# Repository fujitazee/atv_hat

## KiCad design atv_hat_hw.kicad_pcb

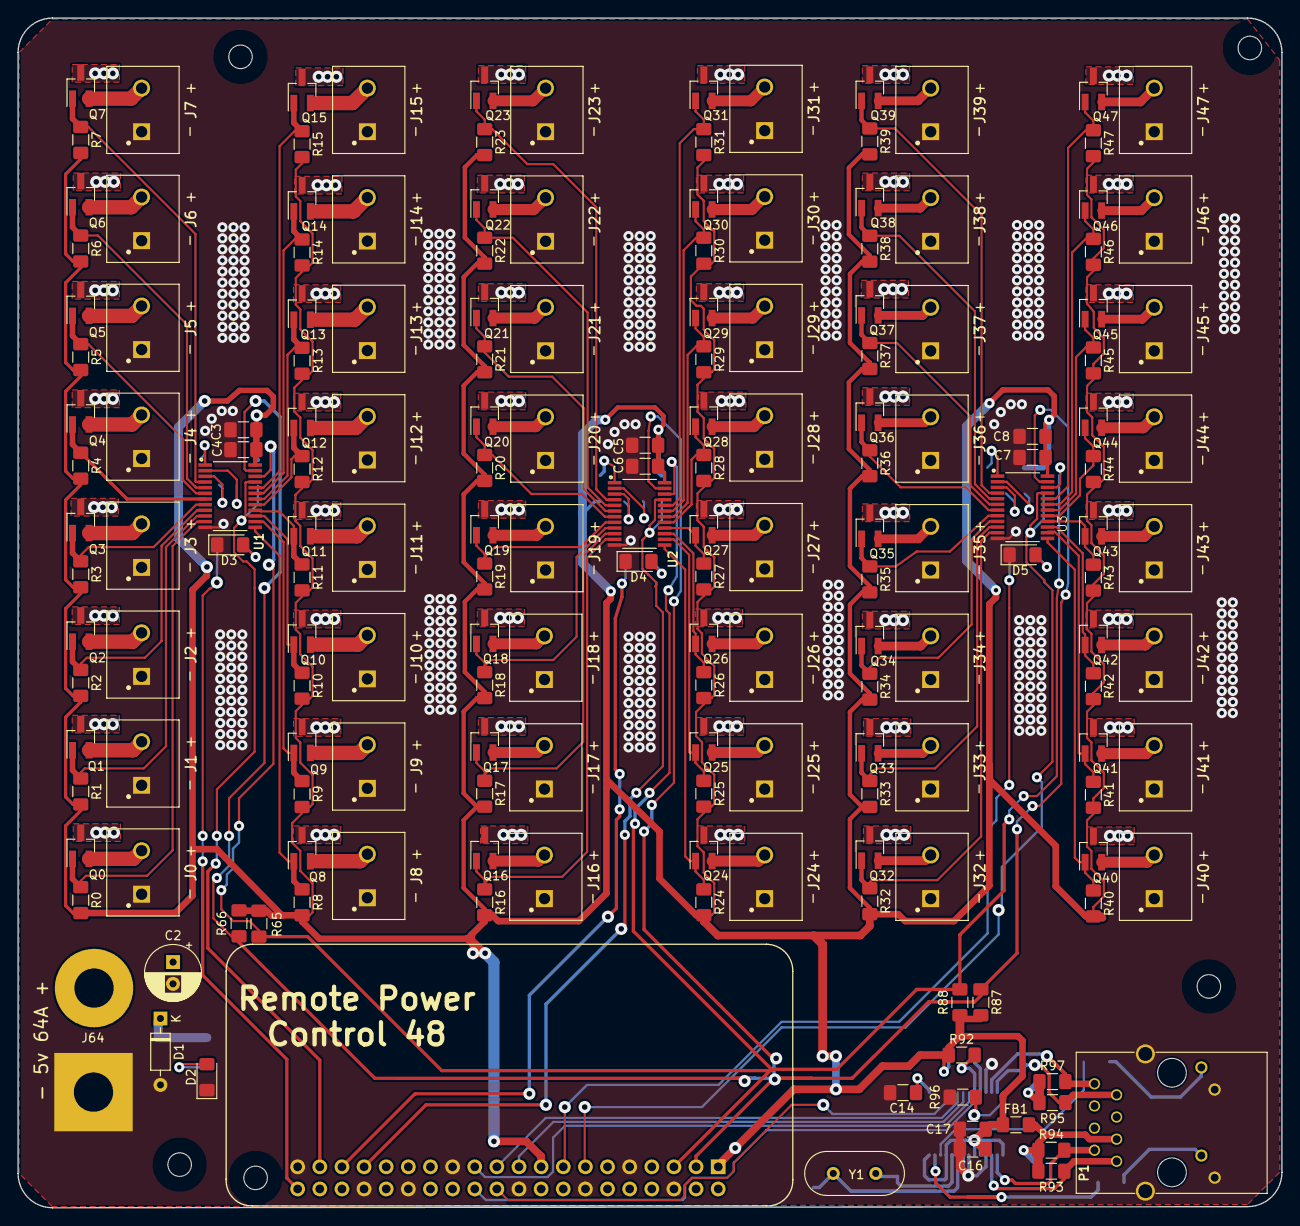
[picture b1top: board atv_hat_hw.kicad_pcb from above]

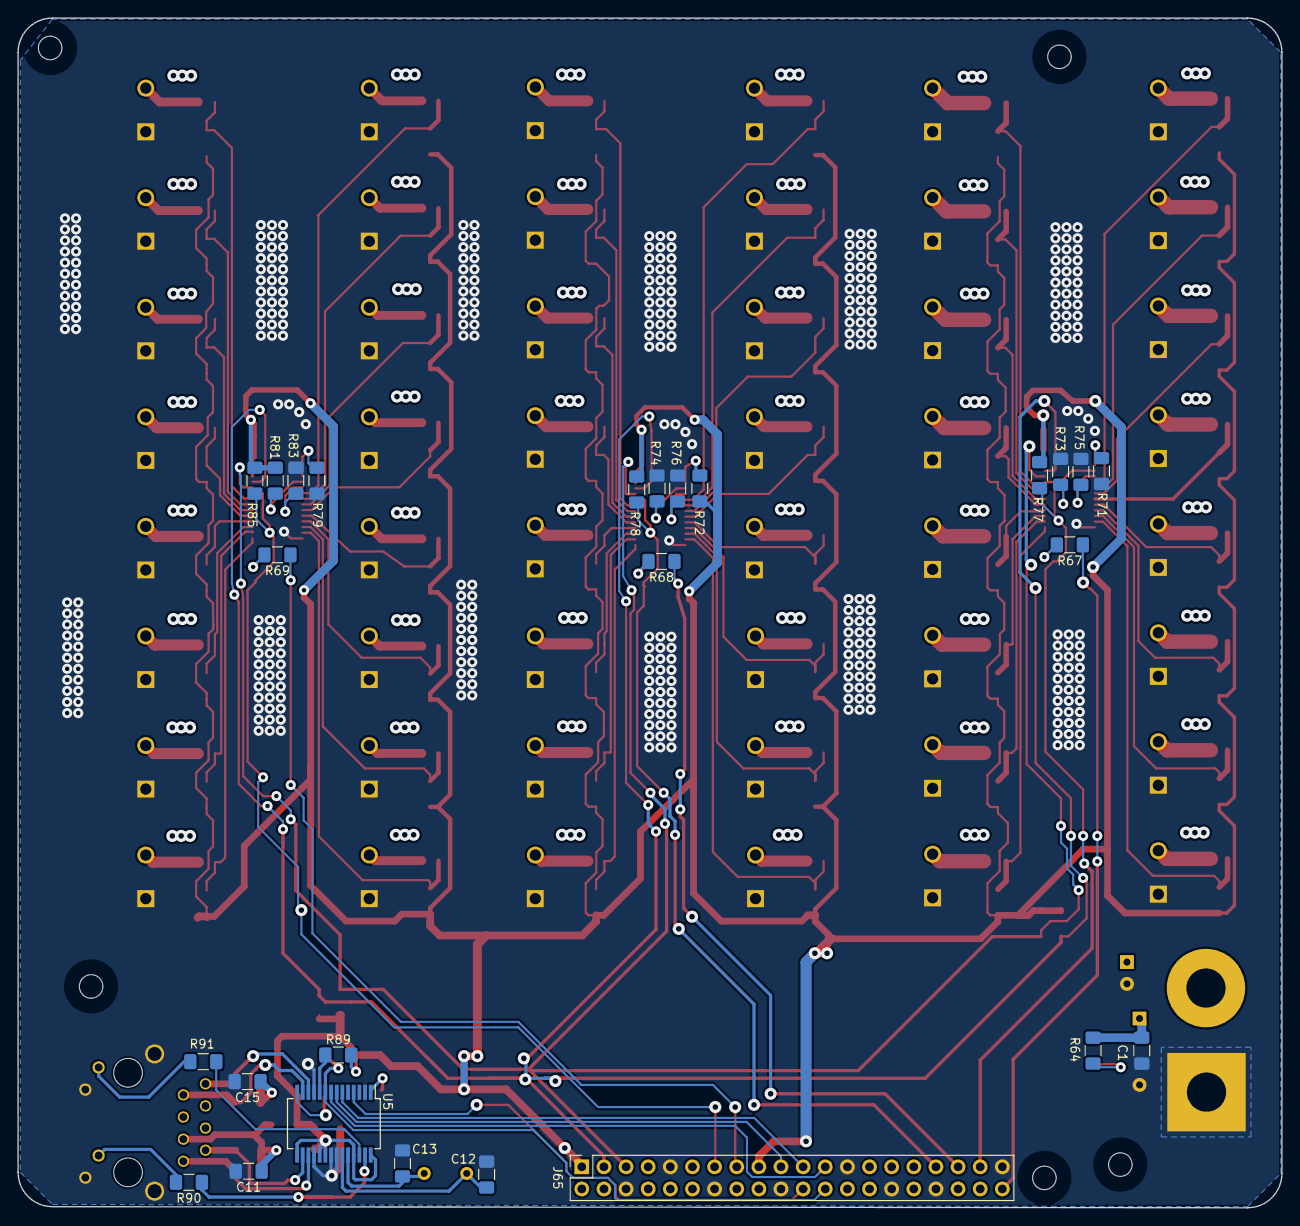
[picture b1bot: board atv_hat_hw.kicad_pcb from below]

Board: 4 copper layers, 145.0 x 136.5 mm, 207 parts (26 on the bottom side), 140 nets.

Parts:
C1, C3, C5, C7, C11, C15, C16: 100n; C_1206_3216Metric_Pad1.42x1.75mm_HandSolder
C2: 100u; CP_Radial_D6.3mm_P2.50mm
C4, C6, C8, C14, C17: 10u; C_1206_3216Metric_Pad1.42x1.75mm_HandSolder
C12, C13: 30p; C_1206_3216Metric_Pad1.42x1.75mm_HandSolder
D1: 5.6v; D_DO-35_SOD27_P7.62mm_Horizontal
D2: Blue; LED_1206_3216Metric_Pad1.42x1.75mm_HandSolder
D3, D4, D5: Green; LED_1206_3216Metric_Pad1.42x1.75mm_HandSolder
FB1: 80mA; L_1206_3216Metric_Pad1.42x1.75mm_HandSolder
H2, H2#2, H2#3, H2#4, H2#5: MountingHole; MountingHole_2.7mm_M2.5_uHAT_RPi
J0, J1, J2, J3, J4, J5, J6, J7, J8, J9, J10, J11, J12, J13, J14, J15, J16, J17, J18, J19, J20, J21, J22, J23, J24, J25, J26, J27, J28, J29, J30, J31, J32, J33, J34, J35, J36, J37, J38, J39, J40, J41, J42, J43, J44, J45, J46, J47: phoenix_1935161; PHOENIX_1935161
J64: phoenix_1935161; SolderWirePad_1x02_P9.0mm_Drill4.5mm
J65: GPIO_CONNECTOR; PinSocket_2x20_P2.54mm_Vertical_Centered_Anchor
P1: RB1-125BAG1A; WIZNET_RB1-125BAG1A
Q0, Q1, Q2, Q3, Q4, Q5, Q6, Q7, Q8, Q9, Q10, Q11, Q12, Q13, Q14, Q15, Q16, Q17, Q18, Q19, Q20, Q21, Q22, Q23, Q24, Q25, Q26, Q27, Q28, Q29, Q30, Q31, Q32, Q33, Q34, Q35, Q36, Q37, Q38, Q39, Q40, Q41, Q42, Q43, Q44, Q45, Q46, Q47: Q_NMOS_GSD; SOT-23_Handsoldering
R0, R1, R2, R3, R4, R5, R6, R7, R8, R9, R10, R11, R12, R13, R14, R15, R16, R17, R18, R19, R20, R21, R22, R23, R24, R25, R26, R27, R28, R29, R30, R31, R32, R33, R34, R35, R36, R37, R38, R39, R40, R41, R42, R43, R44, R45, R46, R47, R65, R66, R71, R72, R73, R74, R75, R76, R77, R78, R79, R81, R83, R85, R87, R88, R89, R90, R91, R92: 10k; R_1206_3216Metric_Pad1.42x1.75mm_HandSolder
R64, R67, R68, R69: 220; R_1206_3216Metric_Pad1.42x1.75mm_HandSolder
R93, R94, R95, R97: 49.9; R_1206_3216Metric_Pad1.42x1.75mm_HandSolder
R96: 2.32k; R_1206_3216Metric_Pad1.42x1.75mm_HandSolder
U1, U2, U3: PCA9552PW,118; SOP65P640X110-24N
U5: ENC28J60x-SS; SSOP-28_5.3x10.2mm_P0.65mm
Y1: Crystal; Crystal_HC49-4H_Vertical

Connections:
+3V3: C3.2, C4.2, C5.2, C6.2, C7.2, C8.2, C16.2, C17.2, FB1.1, J65.1, J65.17, R0.2, R1.2, R2.2, R3.2, R4.2, R5.2, R6.2, R7.2, R8.2, R9.2, R10.2, R11.2, R12.2, R13.2, R14.2, R15.2, R16.2, R17.2, R18.2, R19.2, R20.2, R21.2, R22.2, R23.2, R24.2, R25.2, R26.2, R27.2, R28.2, R29.2, R30.2, R31.2, R32.2, R33.2, R34.2, R35.2, R36.2, R37.2, R38.2, R39.2, R40.2, R41.2, R42.2, R43.2, R44.2, R45.2, R46.2, R47.2, R65.2, R66.2, R72.1, R77.1, R78.1, R81.1, R85.1, R87.2, R88.2, R89.1, R92.1, U1.24, U2.24, U3.24, U5.15, U5.19, U5.20, U5.25, U5.28
+5V: C1.2, C2.1, D1.1, J64.2, J65.2, J65.4, Q0.3, Q1.3, Q2.3, Q3.3, Q4.3, Q5.3, Q6.3, Q7.3, Q8.3, Q9.3, Q10.3, Q11.3, Q12.3, Q13.3, Q14.3, Q15.3, Q16.3, Q17.3, Q18.3, Q19.3, Q20.3, Q21.3, Q22.3, Q23.3, Q24.3, Q25.3, Q26.3, Q27.3, Q28.3, Q29.3, Q30.3, Q31.3, Q32.3, Q33.3, Q34.3, Q35.3, Q36.3, Q37.3, Q38.3, Q39.3, Q40.3, Q41.3, Q42.3, Q43.3, Q44.3, Q45.3, Q46.3, Q47.3, R64.1
/GPIO19: J65.35, R68.1
/GPIO21: J65.40, R67.1
/GPIO22_GEN3: J65.15, R69.1
/ethernet/LEDA: P1.L3, R90.2
/ethernet/LEDB: P1.L1, R91.2
/ethernet/TPIN+: P1.R7, R95.1, U5.13
/ethernet/TPIN-: P1.R8, R97.2, U5.12
/ethernet/TPOUT+: P1.R1, R93.1, U5.17
/ethernet/TPOUT-: P1.R2, R94.2, U5.16
/ethernet/eth_rst: R89.2, U5.10
GND: C1.1, C2.2, C3.1, C4.1, C5.1, C6.1, C7.1, C8.1, C11.2, C12.2, C13.2, C14.1, C15.2, C16.1, C17.1, D1.2, D2.1, D3.1, D4.1, D5.1, J0.1, J1.1, J2.1, J3.1, J4.1, J5.1, J6.1, J7.1, J8.1, J9.1, J10.1, J11.1, J12.1, J13.1, J14.1, J15.1, J16.1, J17.1, J18.1, J19.1, J20.1, J21.1, J22.1, J23.1, J24.1, J25.1, J26.1, J27.1, J28.1, J29.1, J30.1, J31.1, J32.1, J33.1, J34.1, J35.1, J36.1, J37.1, J38.1, J39.1, J40.1, J41.1, J42.1, J43.1, J44.1, J45.1, J46.1, J47.1, J64.1, J65.6, J65.9, J65.14, J65.20, J65.25, J65.30, J65.34, J65.39, P1.L2, P1.L4, P1.S1, P1.S2, R71.1, R73.1, R74.1, R75.1, R76.1, R79.1, R83.1, R96.2, U1.12, U2.12, U3.12, U5.2, U5.11, U5.18, U5.21, U5.22
GPIO8_SPI_CE0_N: J65.24, R92.2, U5.9
GPIO9_SPI_MISO: J65.21, U5.6
GPIO10_SPI_MOSI: J65.19, U5.7
GPIO11_SPI_SCLK: J65.23, U5.8
GPIO25_GEN6: J65.22, U5.4
GPIO_RST_0: J65.37, R77.2, U1.21
GPIO_RST_1: J65.33, R78.2, U2.21
GPIO_RST_2: J65.13, R85.2, U3.21
unnamed: C11.1, FB1.2, P1.R3, R93.2, R94.1
unnamed: C12.1, U5.23, Y1.1
unnamed: C13.1, U5.24, Y1.2
unnamed: C14.2, U5.1
unnamed: C15.1, R95.2, R97.1
unnamed: D2.2, R64.2
unnamed: D3.2, R67.2
unnamed: D4.2, R68.2
unnamed: D5.2, R69.2
unnamed: J0.2, Q0.2
unnamed: J1.2, Q1.2
unnamed: J2.2, Q2.2
unnamed: J3.2, Q3.2
unnamed: J4.2, Q4.2
unnamed: J5.2, Q5.2
unnamed: J6.2, Q6.2
unnamed: J7.2, Q7.2
unnamed: J8.2, Q8.2
unnamed: J9.2, Q9.2
unnamed: J10.2, Q10.2
unnamed: J11.2, Q11.2
unnamed: J12.2, Q12.2
unnamed: J13.2, Q13.2
unnamed: J14.2, Q14.2
unnamed: J15.2, Q15.2
unnamed: J16.2, Q16.2
unnamed: J17.2, Q17.2
unnamed: J18.2, Q18.2
unnamed: J19.2, Q19.2
unnamed: J20.2, Q20.2
unnamed: J21.2, Q21.2
unnamed: J22.2, Q22.2
unnamed: J23.2, Q23.2
unnamed: J24.2, Q24.2
unnamed: J25.2, Q25.2
unnamed: J26.2, Q26.2
unnamed: J27.2, Q27.2
unnamed: J28.2, Q28.2
unnamed: J29.2, Q29.2
unnamed: J30.2, Q30.2
unnamed: J31.2, Q31.2
unnamed: J32.2, Q32.2
unnamed: J33.2, Q33.2
unnamed: J34.2, Q34.2
unnamed: J35.2, Q35.2
unnamed: J36.2, Q36.2
unnamed: J37.2, Q37.2
unnamed: J38.2, Q38.2
unnamed: J39.2, Q39.2
unnamed: J40.2, Q40.2
unnamed: J41.2, Q41.2
unnamed: J42.2, Q42.2
unnamed: J43.2, Q43.2
unnamed: J44.2, Q44.2
unnamed: J45.2, Q45.2
unnamed: J46.2, Q46.2
unnamed: J47.2, Q47.2
unnamed: R71.2, U1.1
unnamed: R72.2, U2.1
unnamed: R73.2, U1.2
unnamed: R74.2, U2.2
unnamed: R75.2, U1.3
unnamed: R76.2, U2.3
unnamed: R79.2, U3.1
unnamed: R81.2, U3.2
unnamed: R83.2, U3.3
unnamed: R90.1, U5.27
unnamed: R91.1, U5.26
unnamed: R96.1, U5.14
SCL: J65.5, R65.1, R88.1, U1.22, U2.22, U3.22
SDA: J65.3, R66.1, R87.1, U1.23, U2.23, U3.23
pwr_toggle_00: Q0.1, R0.1, U1.11
pwr_toggle_01: Q1.1, R1.1, U1.10
pwr_toggle_02: Q2.1, R2.1, U1.9
pwr_toggle_03: Q3.1, R3.1, U1.8
pwr_toggle_04: Q4.1, R4.1, U1.7
pwr_toggle_05: Q5.1, R5.1, U1.6
pwr_toggle_06: Q6.1, R6.1, U1.5
pwr_toggle_07: Q7.1, R7.1, U1.4
pwr_toggle_08: Q8.1, R8.1, U1.13
pwr_toggle_09: Q9.1, R9.1, U1.14
pwr_toggle_10: Q10.1, R10.1, U1.15
pwr_toggle_11: Q11.1, R11.1, U1.16
pwr_toggle_12: Q12.1, R12.1, U1.17
pwr_toggle_13: Q13.1, R13.1, U1.18
pwr_toggle_14: Q14.1, R14.1, U1.19
pwr_toggle_15: Q15.1, R15.1, U1.20
pwr_toggle_16: Q16.1, R16.1, U2.11
pwr_toggle_17: Q17.1, R17.1, U2.10
pwr_toggle_18: Q18.1, R18.1, U2.9
pwr_toggle_19: Q19.1, R19.1, U2.8
pwr_toggle_20: Q20.1, R20.1, U2.7
pwr_toggle_21: Q21.1, R21.1, U2.6
pwr_toggle_22: Q22.1, R22.1, U2.5
pwr_toggle_23: Q23.1, R23.1, U2.4
pwr_toggle_24: Q24.1, R24.1, U2.13
pwr_toggle_25: Q25.1, R25.1, U2.14
pwr_toggle_26: Q26.1, R26.1, U2.15
pwr_toggle_27: Q27.1, R27.1, U2.16
pwr_toggle_28: Q28.1, R28.1, U2.17
pwr_toggle_29: Q29.1, R29.1, U2.18
pwr_toggle_30: Q30.1, R30.1, U2.19
pwr_toggle_31: Q31.1, R31.1, U2.20
pwr_toggle_32: Q32.1, R32.1, U3.11
pwr_toggle_33: Q33.1, R33.1, U3.10
pwr_toggle_34: Q34.1, R34.1, U3.9
pwr_toggle_35: Q35.1, R35.1, U3.8
pwr_toggle_36: Q36.1, R36.1, U3.7
pwr_toggle_37: Q37.1, R37.1, U3.6
pwr_toggle_38: Q38.1, R38.1, U3.5
pwr_toggle_39: Q39.1, R39.1, U3.4
pwr_toggle_40: Q40.1, R40.1, U3.13
pwr_toggle_41: Q41.1, R41.1, U3.14
pwr_toggle_42: Q42.1, R42.1, U3.15
pwr_toggle_43: Q43.1, R43.1, U3.16
pwr_toggle_44: Q44.1, R44.1, U3.17
pwr_toggle_45: Q45.1, R45.1, U3.18
pwr_toggle_46: Q46.1, R46.1, U3.19
pwr_toggle_47: Q47.1, R47.1, U3.20

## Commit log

2020-06-30 Initial commit with 6 device control
2020-07-07 plus board ready for routing
2020-08-07 64 port hat
2020-08-07 PCB routed for 48 ports
2020-08-29 Added in boilerplate for control script
2020-08-30 Added led control using RPi.GPIO library
2020-08-30 Added get state for leds
2020-08-31 Added look up table for i2c data to be written
2020-08-31 port power control working
2020-08-31 Added configuration template for fan control
2020-09-01 Added last of atv hat functions and place holder for monitor script
2023-12-20 adding updated reboot all script
2024-05-12 better version of atv hat controller just using a socket

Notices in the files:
atv_hat_hw.kicad_pcb:
This PCB design is licensed under MIT Open Source License.
